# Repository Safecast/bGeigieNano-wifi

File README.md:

This project is designed to provide a simple wifi interface for the bGeigieNano for use as a fixed sensor. It it would sit on the XBee header and receive data from the Arduino. This data would then be reformatted as JSON for upload to the safecast servers.

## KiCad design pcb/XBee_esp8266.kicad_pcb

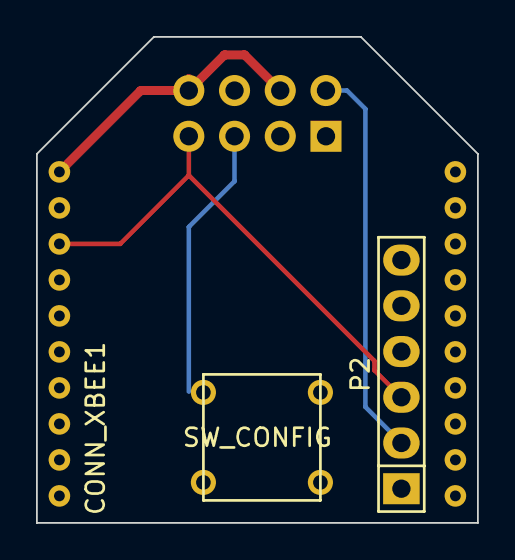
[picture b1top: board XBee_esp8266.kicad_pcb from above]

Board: 2 copper layers, 24.5 x 27.0 mm, 5 parts (1 on the bottom side), 5 nets.

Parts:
P1: CONN_XBEE1; 1x10_2MM
P2: CONN_SERIAL; Pin_Header_Straight_1x06
P3: CONN_ESP8266; Pin_Header_Straight_2x04
P4: CONN_XBEE2; 1x10_2MM
SW1: SW_CONFIG; SW_PUSH_SMALL

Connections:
+3.3V: P1.1, P3.4, P3.8
GND: P1.10, P2.6, P3.1, SW1.2
unnamed: P1.3, P2.3, P3.7
unnamed: P2.2, P3.2
unnamed: P3.5, SW1.1

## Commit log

2015-01-06 Initial version, proof of concept transmission of a fixed JSON string to dev server.
2015-01-06 added sscanf implementation (work in progress)
2015-01-06 test parsing on nema string
2015-01-07 fixing nsscaf...
2015-01-07 Parsing nema, creating json and sending to API appears to be working correctly.
2015-01-08 uart receive code in place. fix issue with wifi connect
2015-01-08 appears to be parsing line data from client and sending to safecast servers correctly. Needs testing on real hardware
2015-01-09 Fixed variable name, reset connection on DNS lookup fail
2015-01-09 XBee carrier board design/gerbers. GPIO check
2015-01-12 SSID,Password, and APIKEY are stored in user flash. Can be configured from built in HTTP server. Requires extra functionality to deal with initial setting
2015-01-13 complete basic functionality is in place, press GPIO to enter AP mode. Connect to ESP_XXXX network, host 192.168.4.1 to config (user 192.168.4.1/ERASE to erase all settings)
2015-01-26 added TODO, various fixes. Reset ap mode after any reset
2015-01-26 updated gerbers
2015-03-03 added 5min interval functionality, hopefully fixed some issues with flash configuration
2015-03-10 allow selection between safecast development and live servers
2015-03-10 fixed a couple of typos in the license file
2015-03-10 appears to be working correctly now. crashing on flash writes seem to be fixed, as do checkbox settings
